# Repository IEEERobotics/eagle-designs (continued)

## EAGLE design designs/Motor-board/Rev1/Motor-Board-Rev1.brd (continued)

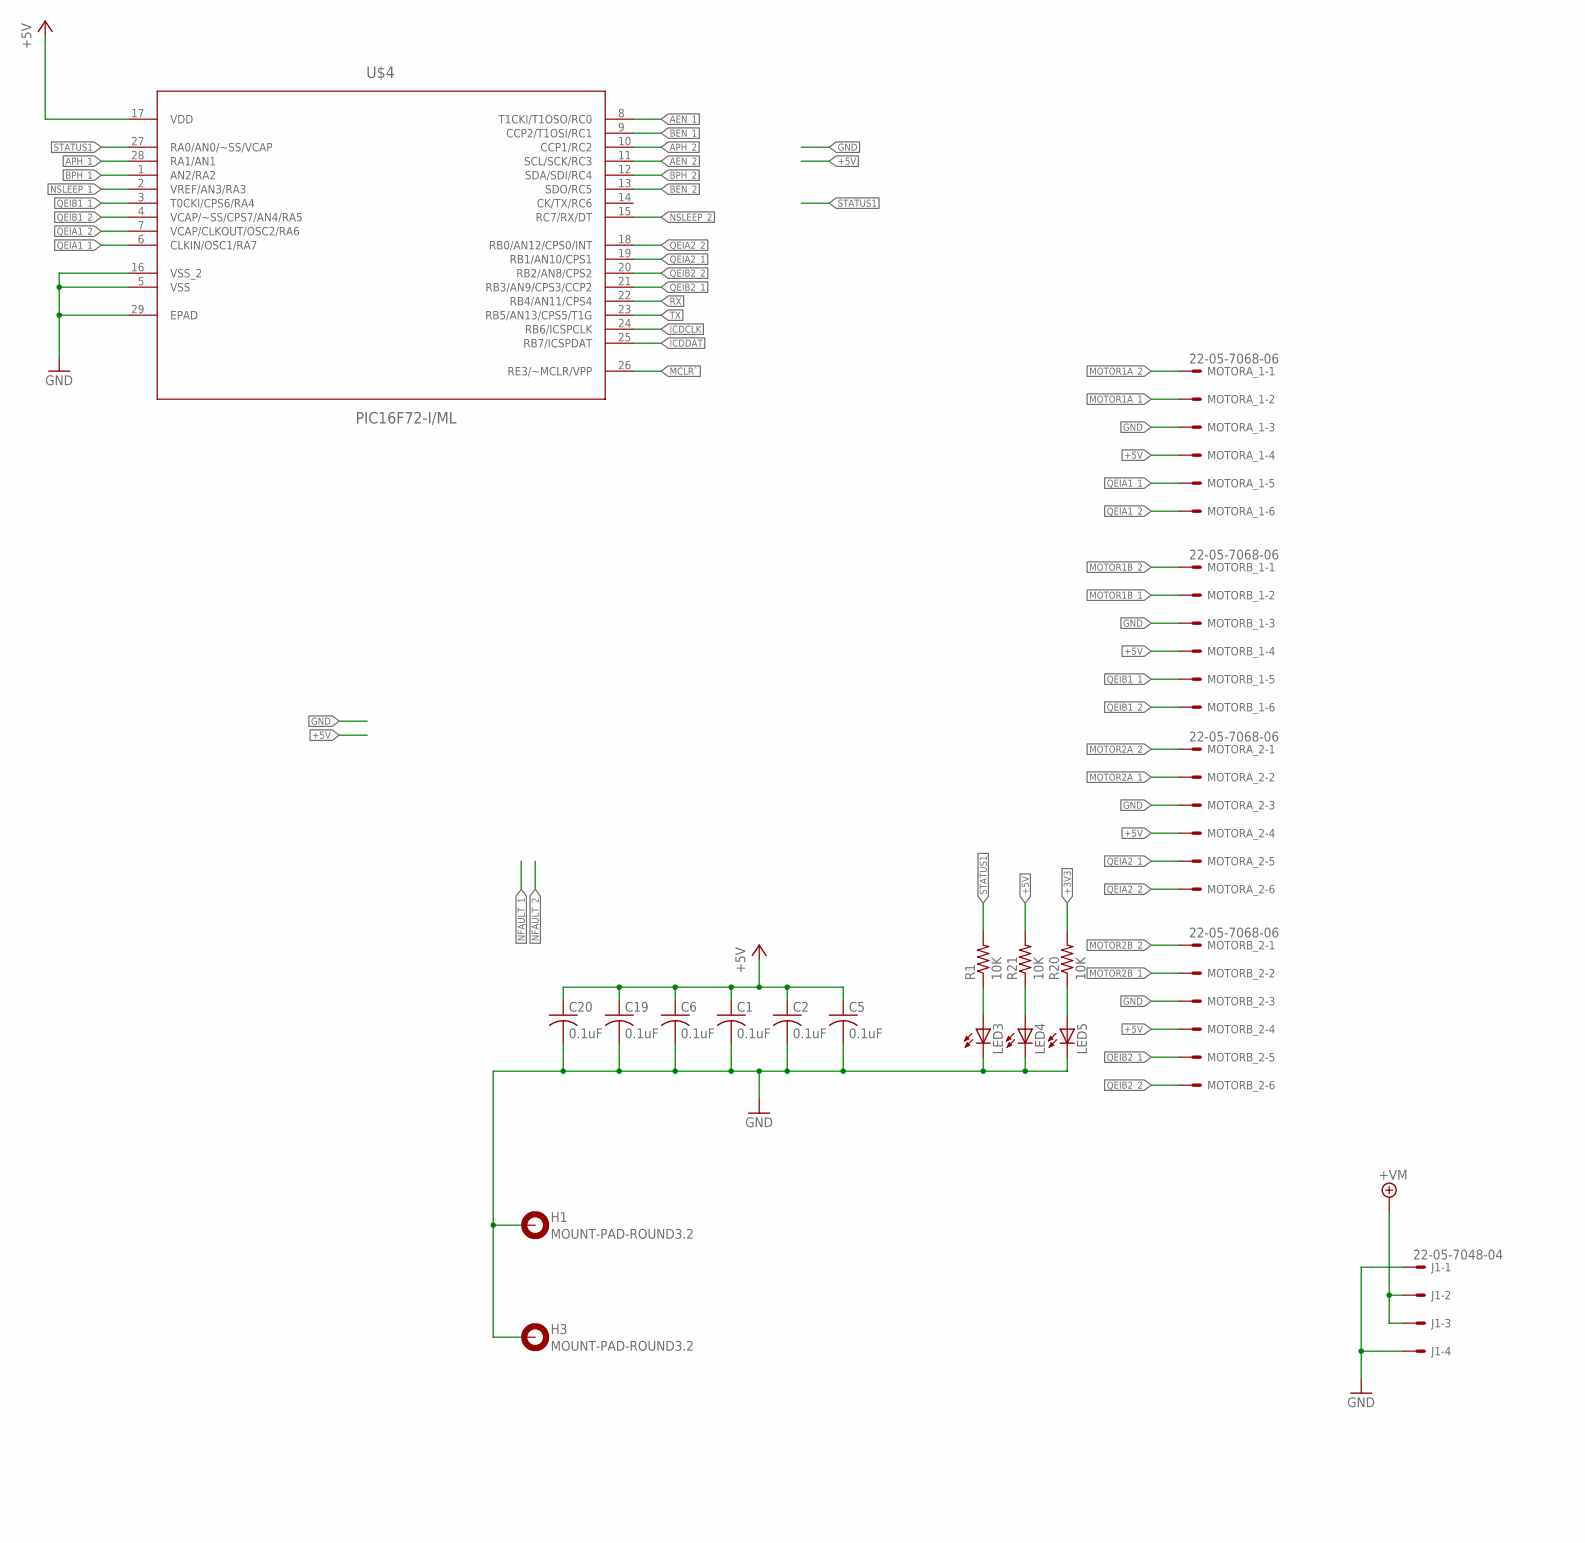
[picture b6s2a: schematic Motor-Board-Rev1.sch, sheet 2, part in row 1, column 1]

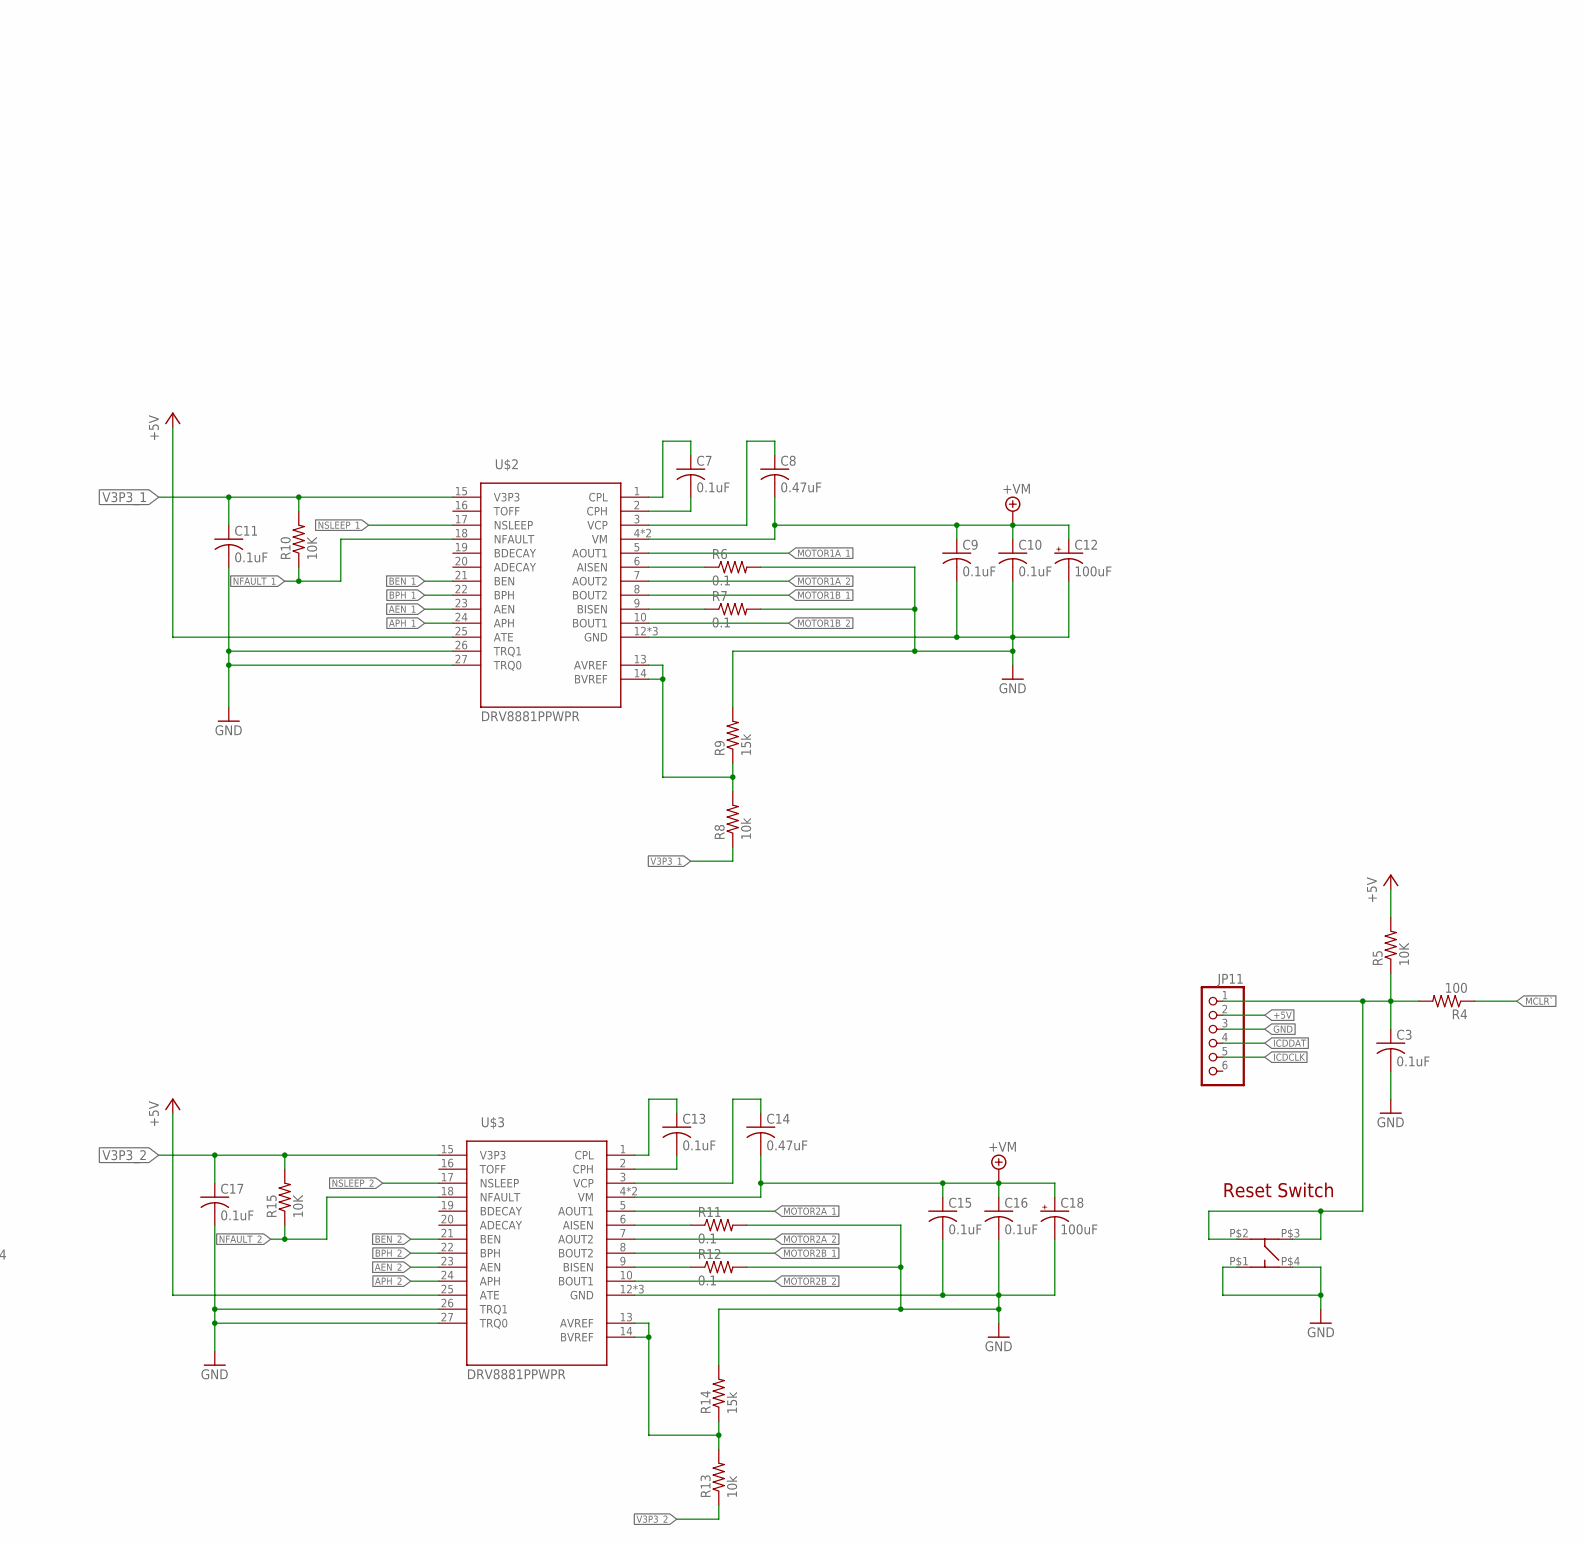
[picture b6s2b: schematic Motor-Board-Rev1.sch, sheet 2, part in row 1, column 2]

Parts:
C1, C2, C3, C5, C6, C19, C20: 0.1uF; C0805
C7, C9, C10, C11, C13, C15, C16, C17: 0.1uF; C0402
C8, C14: 0.47uF; C0402
C12, C18: 100uF; EIA7343
H1, H3: MOUNT-PAD-ROUND3.2; 3,2-PAD
J1: 22-05-7048-04; 7395-04
JP11: PINHD-1X6/90; 1X06/90
LED3, LED4, LED5: LEDSML0603; SML0603
MOTORA_1, MOTORA_2: 22-05-7068-06; 7395-06
MOTORB_1, MOTORB_2: 22-05-7068-06; 7395-06
R1, R5, R20, R21: 10K; R0805
R4: 100; R0805
R6, R7, R11, R12: 0.1; R1206
R8, R13: 10k; R0402
R9, R14: 15k; R0402
R10, R15: 10K; R1206
TOUCH_RESET: RESET; MC32882_FINAL
U$2, U$3: DRV8881PPWPR; TSSOP-28
U$4: PIC16F72-I/ML; QFN65P600X600X100-28N

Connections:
+3V3: R20.2; also elsewhere on the board
+5V: C1.1, C2.1, C5.1, C6.1, C19.1, C20.1, JP11.2, MOTORA_1.4, MOTORA_2.4, MOTORB_1.4, MOTORB_2.4, R5.2, R21.2, U$2.25 (ATE), U$3.25 (ATE), U$4.17 (VDD); also elsewhere on the board
+7V: C8.2, C9.1, C10.1, C12.A (+), C14.2, C15.1, C16.1, C18.A (+), J1.2, J1.3, U$2.4 (VM), U$2.11 (VM), U$3.4 (VM), U$3.11 (VM)
AEN_1: U$2.23 (AEN), U$4.8 (T1CKI/T1OSO/RC0)
AEN_2: U$3.23 (AEN), U$4.11 (SCL/SCK/RC3)
APH_1: U$2.24 (APH), U$4.28 (RA1/AN1)
APH_2: U$3.24 (APH), U$4.10 (CCP1/RC2)
BEN_1: U$2.21 (BEN), U$4.9 (CCP2/T1OSI/RC1)
BEN_2: U$3.21 (BEN), U$4.13 (SDO/RC5)
BPH_1: U$2.22 (BPH), U$4.1 (AN2/RA2)
BPH_2: U$3.22 (BPH), U$4.12 (SDA/SDI/RC4)
GND: C1.2, C2.2, C3.2, C5.2, C6.2, C9.2, C10.2, C11.2, C12.C (-), C15.2, C16.2, C17.2, C18.C (-), C19.2, C20.2, H1.B3,2, H3.B3,2, J1.1, J1.4, JP11.3, LED3.C, LED4.C, LED5.C, MOTORA_1.3, MOTORA_2.3, MOTORB_1.3, MOTORB_2.3, R6.2, R7.2, R9.2, R11.2, R12.2, R14.2, TOUCH_RESET.P$1 (P1), TOUCH_RESET.P$4 (P4), U$2.12 (GND), U$2.26 (TRQ1), U$2.27 (TRQ0), U$2.28 (GND), U$2.EXP (GND), U$3.12 (GND), U$3.26 (TRQ1), U$3.27 (TRQ0), U$3.28 (GND), U$3.EXP (GND), U$4.5 (VSS), U$4.16 (VSS_2), U$4.29 (EPAD); also elsewhere on the board
ICDCLK: JP11.5, U$4.24 (RB6/ICSPCLK)
ICDDAT: JP11.4, U$4.25 (RB7/ICSPDAT)
MCLR: C3.1, JP11.1, R4.2, R5.1, TOUCH_RESET.P$2 (P2), TOUCH_RESET.P$3 (P3)
MCLR`: R4.1, U$4.26 (RE3/~MCLR/VPP)
MOTOR1A_1: MOTORA_1.2, U$2.5 (AOUT1)
MOTOR1A_2: MOTORA_1.1, U$2.7 (AOUT2)
MOTOR1B_1: MOTORB_1.2, U$2.8 (BOUT2)
MOTOR1B_2: MOTORB_1.1, U$2.10 (BOUT1)
MOTOR2A_1: MOTORA_2.2, U$3.5 (AOUT1)
MOTOR2A_2: MOTORA_2.1, U$3.7 (AOUT2)
MOTOR2B_1: MOTORB_2.2, U$3.8 (BOUT2)
MOTOR2B_2: MOTORB_2.1, U$3.10 (BOUT1)
unnamed: LED3.A, R1.1
unnamed: R7.1, U$2.9 (BISEN)
unnamed: LED5.A, R20.1
unnamed: LED4.A, R21.1
unnamed: R6.1, U$2.6 (AISEN)
unnamed: C7.2, U$2.2 (CPH)
unnamed: C7.1, U$2.1 (CPL)
unnamed: C8.1, U$2.3 (VCP)
unnamed: R8.2, R9.1, U$2.13 (AVREF), U$2.14 (BVREF)
unnamed: R12.1, U$3.9 (BISEN)
unnamed: R11.1, U$3.6 (AISEN)
unnamed: C13.2, U$3.2 (CPH)
unnamed: C13.1, U$3.1 (CPL)
unnamed: C14.1, U$3.3 (VCP)
unnamed: R13.2, R14.1, U$3.13 (AVREF), U$3.14 (BVREF)
NFAULT_1: R10.1, U$2.18 (NFAULT)
NFAULT_2: R15.1, U$3.18 (NFAULT)
NSLEEP_1: U$2.17 (NSLEEP), U$4.2 (VREF/AN3/RA3)
NSLEEP_2: U$3.17 (NSLEEP), U$4.15 (RC7/RX/DT)
QEIA1_1: MOTORA_1.5, U$4.6 (CLKIN/OSC1/RA7)
QEIA1_2: MOTORA_1.6, U$4.7 (VCAP/CLKOUT/OSC2/RA6)
QEIA2_1: MOTORA_2.5, U$4.19 (RB1/AN10/CPS1)
QEIA2_2: MOTORA_2.6, U$4.18 (RB0/AN12/CPS0/INT)
QEIB1_1: MOTORB_1.5, U$4.3 (T0CKI/CPS6/RA4)
QEIB1_2: MOTORB_1.6, U$4.4 (VCAP/~SS/CPS7/AN4/RA5)
QEIB2_1: MOTORB_2.5, U$4.21 (RB3/AN9/CPS3/CCP2)
QEIB2_2: MOTORB_2.6, U$4.20 (RB2/AN8/CPS2)
RX: U$4.22 (RB4/AN11/CPS4); also elsewhere on the board
STATUS1: R1.2, U$4.27 (RA0/AN0/~SS/VCAP)
TX: U$4.23 (RB5/AN13/CPS5/T1G); also elsewhere on the board
V3P3_1: C11.1, R8.1, R10.2, U$2.15 (V3P3)
V3P3_2: C17.1, R13.1, R15.2, U$3.15 (V3P3)

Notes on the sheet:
Reset Switch

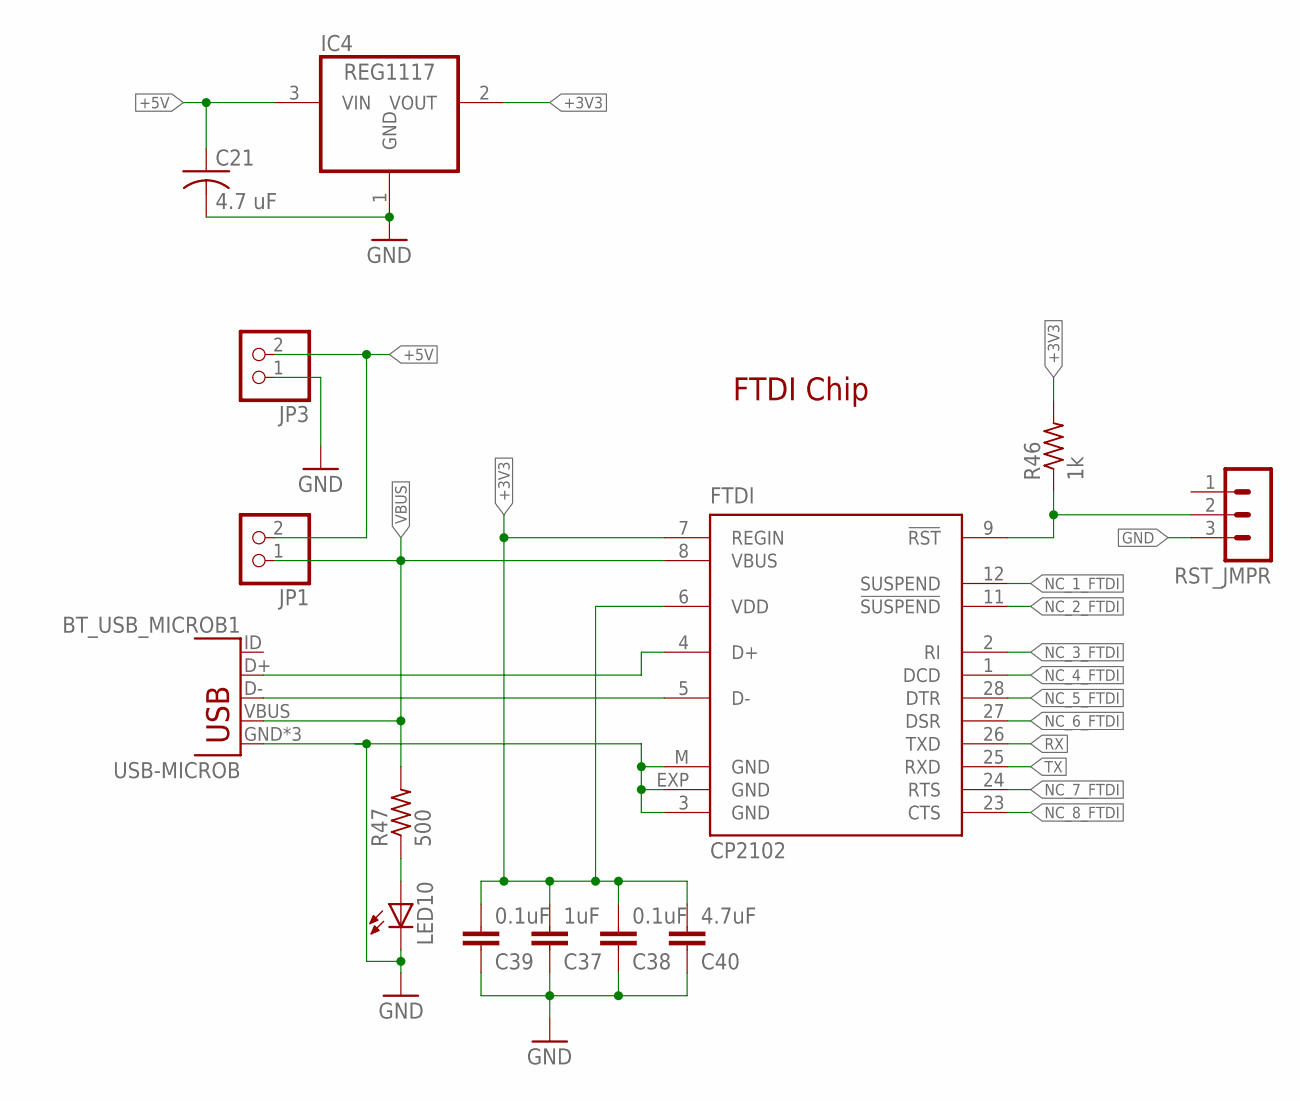
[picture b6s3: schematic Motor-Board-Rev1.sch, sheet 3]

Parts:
BT_USB_MICROB1: USB-MICROB
C21: 4.7 uF; C0805
C37: 1uF; C0805
C38, C39: 0.1uF; C0805
C40: 4.7uF; C0805
FTDI: CP2102; MLP28
IC4: REG1117; SOT223
JP1, JP3: PINHD-1X2; 1X02
LED10: LEDSML0603; SML0603
R46: 1k; R0805
R47: 500; R0805
RST_JMPR: MA03-1

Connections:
+3V3: C37.2, C38.2, C39.2, C40.2, FTDI.6 (VDD), FTDI.7 (REGIN), IC4.2 (VOUT), R46.2; also elsewhere on the board
+5V: C21.1, IC4.3 (VIN), JP1.2, JP3.2; also elsewhere on the board
BT_D+: BT_USB_MICROB1.D+, FTDI.4 (D+)
BT_D-: BT_USB_MICROB1.D-, FTDI.5 (D-)
GND: BT_USB_MICROB1.GND, BT_USB_MICROB1.MT1 (GND), BT_USB_MICROB1.MT2 (GND), C21.2, C37.1, C38.1, C39.1, C40.1, FTDI.3 (GND), FTDI.EXP (GND), FTDI.M (GND), IC4.1 (GND), JP3.1, LED10.C, RST_JMPR.3; also elsewhere on the board
unnamed: FTDI.9 (!RST), R46.1, RST_JMPR.2
unnamed: LED10.A, R47.1
NC_1_FTDI: FTDI.12 (SUSPEND)
NC_2_FTDI: FTDI.11 (!SUSPEND)
NC_3_FTDI: FTDI.2 (RI)
NC_4_FTDI: FTDI.1 (DCD)
NC_5_FTDI: FTDI.28 (DTR)
NC_6_FTDI: FTDI.27 (DSR)
NC_7_FTDI: FTDI.24 (RTS)
NC_8_FTDI: FTDI.23 (CTS)
RX: FTDI.26 (TXD); also elsewhere on the board
TX: FTDI.25 (RXD); also elsewhere on the board
VBUS: BT_USB_MICROB1.VBUS, FTDI.8 (VBUS), JP1.1, R47.2

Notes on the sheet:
FTDI Chip

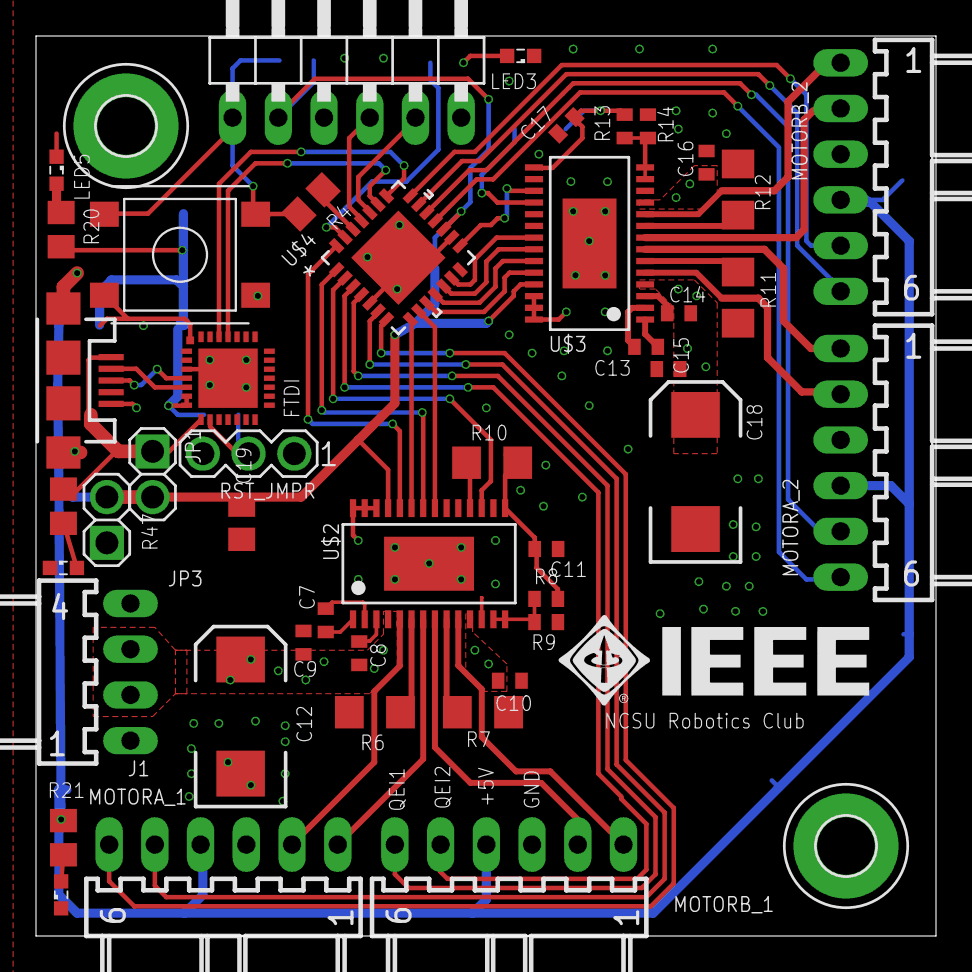
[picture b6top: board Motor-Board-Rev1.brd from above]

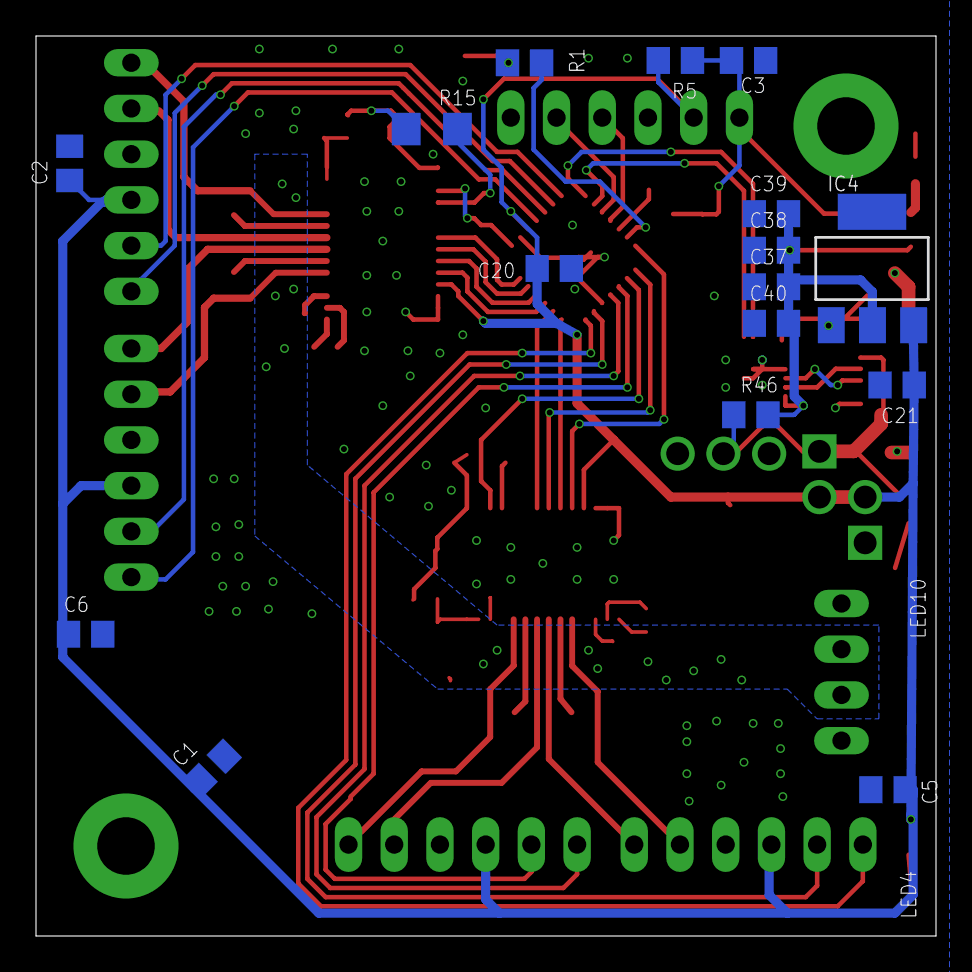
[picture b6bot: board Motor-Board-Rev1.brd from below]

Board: 2 copper layers, 50.0 x 50.0 mm, 64 parts (16 on the bottom side), 61 nets.

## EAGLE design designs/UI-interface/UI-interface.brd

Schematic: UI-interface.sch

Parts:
D1: 1N4148; SOD-323F
H1, H2: MOUNT-PAD-ROUND3.0; 3,0-PAD
JP1: HEADER-1X670MIL; 1X06_ROUND_70
R5: 10K; 0805

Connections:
3.3V: JP1.2, R5.2
GND: JP1.3
RES_3.3V: D1.A, R5.1
RES_5.0V: D1.C, JP1.4
SCL_5.0V: JP1.5
SDA_5.0V: JP1.6
VIN: JP1.1

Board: 2 copper layers, 5 parts (0 on the bottom side), 3 nets, no tracks yet.

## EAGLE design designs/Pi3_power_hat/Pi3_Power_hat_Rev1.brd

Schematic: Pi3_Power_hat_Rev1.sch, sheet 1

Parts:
LED3: LEDCHIP-LED0603; CHIP-LED0603
PL12: 555X-2H; 5569-2
R15: 330; R0402
X1: RASPI_BOARD_B+#_E4P; RASPI_BOARD_B+_EDGES_4DRILL_PAD

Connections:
3V3A: X1.1 (3V3A)
3V3B: X1.17 (3V3B)
5V0A: X1.2 (5V0A)
5V0B: X1.4 (5V0B)
GND: LED3.C, PL12.1; also elsewhere on the board
GND_A: X1.6 (GND_A)
GND_B: X1.9 (GND_B)
GND_C: X1.14 (GND_C)
GND_D: X1.20 (GND_D)
GND_E: X1.25 (GND_E)
GND_F: X1.30 (GND_F)
GND_G: X1.34 (GND_G)
GND_H: X1.39 (GND_H)
unnamed: LED3.A, R15.1
VCC: PL12.2, R15.2; also elsewhere on the board

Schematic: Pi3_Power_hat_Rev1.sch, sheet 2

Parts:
C1: .1uF; C0402
C2: 4.7pF; C0402
C3, C5, C7: 1uF; C0402
C4: 47uF; C1210
C6: 10nF; C0402
C8: 4.7uF; C0603
J1, J2, J3: 22-05-7028-02; 7395-02
L1: 4.7uH; IHLP2525EZER4R7M01-FOOT
LED2: LEDCHIP-LED0603; CHIP-LED0603
R1: 1M; R0402
R2: 88.7k; R0402
R3: 41.2K; R0402
R4: 10k; R0402
R14: 1.2k; R0402
U$1: LT8640; LT8640_FOOT

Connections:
+12V: C2.1, C4.1, J1.2, J2.2, J3.2, L1.2, R1.2, R4.2, R14.2, U$1.1 (BIAS)
GND: C3.2, C4.2, C5.2, C6.2, C7.2, C8.2, J1.1, J2.1, J3.1, LED2.C, R2.1, R3.2, U$1.6 (GND1), U$1.7 (GND1), U$1.10 (GND2), U$1.11 (GND2), U$1.18 (GND); also elsewhere on the board
unnamed: C1.1, U$1.3 (BST)
unnamed: C1.2, L1.1, U$1.8 (SW), U$1.9 (SW), U$1.21 (SW), U$1.22 (SW)
unnamed: R4.1, U$1.19 (PG)
unnamed: C2.2, R1.1, R2.2, U$1.20 (FB)
unnamed: C6.1, U$1.16 (TR/SS)
unnamed: C5.1, U$1.2 (INTV)
unnamed: R3.1, U$1.15 (RT)
unnamed: LED2.A, R14.1
VCC: C3.1, C7.1, C8.1, U$1.4 (VIN1), U$1.13 (VIN2); also elsewhere on the board

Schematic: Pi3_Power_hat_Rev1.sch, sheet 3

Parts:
C9: .1uF; C0402
C10: 4.7pF; C0402
C11, C13, C15: 1uF; C0402
C12: 47uF; C1210
C14: 10nF; C0402
C16: 4.7uF; C0603
J4, J5, J6: 22-05-7028-02; 7395-02
L2: 1.5uH; IHLP2525EZER4R7M01-FOOT
LED1: LEDCHIP-LED0603; CHIP-LED0603
R5: 1M; R0402
R6: 200k; R0402
R7: 18.2k; R0402
R8: 10k; R0402
R13: 600; R0402
U$2: LT8640; LT8640_FOOT

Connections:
+6V: C10.1, C12.1, J4.2, J5.2, J6.2, L2.2, R5.2, R8.2, R13.2, U$2.1 (BIAS)
GND: C11.2, C12.2, C13.2, C14.2, C15.2, C16.2, J4.1, J5.1, J6.1, LED1.C, R6.1, R7.2, U$2.6 (GND1), U$2.7 (GND1), U$2.10 (GND2), U$2.11 (GND2), U$2.18 (GND); also elsewhere on the board
unnamed: C9.1, U$2.3 (BST)
unnamed: C9.2, L2.1, U$2.8 (SW), U$2.9 (SW), U$2.21 (SW), U$2.22 (SW)
unnamed: C10.2, R5.1, R6.2, U$2.20 (FB)
unnamed: C14.1, U$2.16 (TR/SS)
unnamed: C13.1, U$2.2 (INTV)
unnamed: R7.1, U$2.15 (RT)
unnamed: R8.1, U$2.19 (PG)
unnamed: LED1.A, R13.1
VCC: C11.1, C15.1, C16.1, U$2.4 (VIN1), U$2.13 (VIN2); also elsewhere on the board

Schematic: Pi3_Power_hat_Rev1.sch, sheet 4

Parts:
C17: .1uF; C0402
C18: 4.7pF; C0402
C19, C21, C23: 1uF; C0402
C20: 47uF; C1210
C22: 10nF; C0402
C24: 4.7uF; C0603
J7, J8, J9: 22-05-7028-02; 7395-02
L3: 1.5uH; IHLP2525EZER4R7M01-FOOT
LED14: LEDCHIP-LED0603; CHIP-LED0603
R9: 1M; R0402
R10: 243k; R0402
R11: 18.2k; R0402
R12: 10k; R0402
R18: 500\; R0402
U$3: LT8640; LT8640_FOOT

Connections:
+5V: C18.1, C20.1, J7.2, J8.2, J9.2, L3.2, R9.2, R12.2, R18.2, U$3.1 (BIAS)
GND: C19.2, C20.2, C21.2, C22.2, C23.2, C24.2, J7.1, J8.1, J9.1, LED14.C, R10.1, R11.2, U$3.6 (GND1), U$3.7 (GND1), U$3.10 (GND2), U$3.11 (GND2), U$3.18 (GND); also elsewhere on the board
unnamed: C17.1, U$3.3 (BST)
unnamed: C17.2, L3.1, U$3.8 (SW), U$3.9 (SW), U$3.21 (SW), U$3.22 (SW)
unnamed: C18.2, R9.1, R10.2, U$3.20 (FB)
unnamed: C22.1, U$3.16 (TR/SS)
unnamed: C21.1, U$3.2 (INTV)
unnamed: R11.1, U$3.15 (RT)
unnamed: R12.1, U$3.19 (PG)
unnamed: LED14.A, R18.1
VCC: C19.1, C23.1, C24.1, U$3.4 (VIN1), U$3.13 (VIN2); also elsewhere on the board

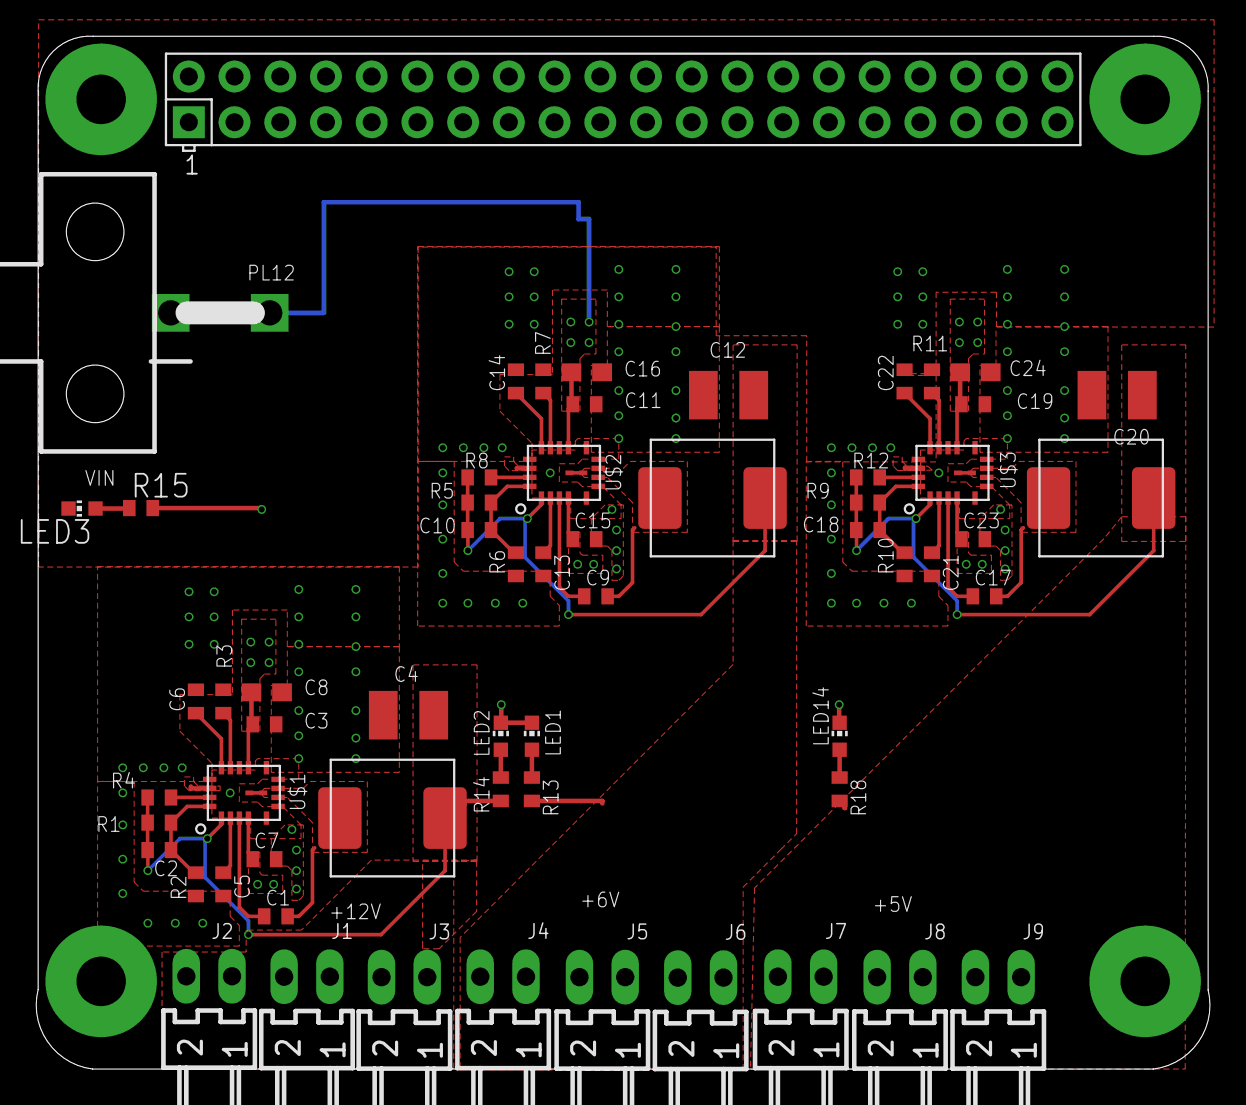
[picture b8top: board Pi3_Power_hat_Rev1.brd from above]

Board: 2 copper layers, 65.2 x 57.4 mm, 61 parts (0 on the bottom side), 30 nets.

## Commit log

2015-04-01 updeate to values on the ADC cape rev 3
2015-04-20 Adding more libs
2015-04-20 adding initial board files
2015-04-22 Adding bord file for lcd screen
2015-04-22 adding board files for adc board
2015-04-22 adding files for range cape
2015-04-22 done with range cape
2015-05-27 pushing up frist rev of some capes
2015-06-26 created geber files for range cap rev2
2015-06-26 Added arduino lib
2015-06-26 fixed rev 2
2015-06-26 done with rev 3
2015-06-26 need to fix qfn pad and level shifer
2015-07-15 Done with son of dark power and starting to woek one servo cape
2015-08-10 Flyback Cape
2015-09-21 servo cape
2015-10-02 Adding files for old Dark Power
2015-10-04 Need to add switch
2015-10-07 Done with rev 2
2015-10-07 Adding files for gerber files for Dark Power rev 2
2015-10-14 ready to be sent to board house
2015-10-14 Ready to be sent to part house
2015-10-14 cleaning up
2015-10-14 Remaing Files
2015-10-15 eagle class
2015-10-23 reverting changes back to rev 1
2015-10-23 Readding rev2 to the repo
2015-10-23 Update to the BOM
2015-11-25 Updating servo cape
2015-11-25 Add servo cape rev2 board file
2015-12-18 first commit of motherboard
2015-12-21 added QFN PIC
2015-12-22 last commit of rev 1
2015-12-22 Adding rev 2
2015-12-22 Renaming to rev2
2015-12-24 More work done on motherboard
2015-12-26 Running traces on motherboard
2015-12-28 Done with initial layout
2015-12-29 Done moving labels
2015-12-31 Done with left side of mother board
2015-12-31 Fixed merge
2015-12-31 add logo
2015-12-31 Final Motherboard
2016-01-01 final commit of motherboard
2016-01-01 Add rule files
2016-01-01 Done with Motherboard
2016-01-02 Added values for some of the capactiors
2016-01-02 final
2016-01-13 ADD rplider board
2016-05-21 Motor board
2016-05-31 Add part for Pi3 hats
2016-08-12 Working on motherboard for pi3
2016-08-23 done wiht motherboard
2016-12-21 commit unknown circuit
2016-12-22 Updated Unknown Circuit Schematic
2016-12-22 Uploaded IR Interface Board Schematic
2016-12-22 Fix Resistor values
2016-12-22 Fiexd +5 V
2016-12-23 Done with Unknow circuit
2016-12-24 Finished layout. Kind of rushed. Probably needs a second set of eyes.
2016-12-24 Done with Unknown
2016-12-24 Setting init dim for ui board
2016-12-28 done with first version of the boards
2017-01-10 fixed air wires
2017-01-10 Fixing headers
2017-02-14 adding the revised stepper board
2017-02-14 removed extra part
2017-02-22 Add files via upload
    work in progress layout for stepper board
2017-02-24 adding out of sync local files
2017-03-14 Finished Rev3 of IR Interface Board, and generated gerber files.
2017-03-14 Added Rev3 folder.
